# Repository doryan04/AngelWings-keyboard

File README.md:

# Angel Wings Keyboard (by [@ItzAdel](https://github.com/doryan04) and [@nm17](https://github.com/nm17))

.jpg)

# Keymap

The Lower, Raise and Adjust layers are provided to allow you to use full-size keys that are not on this keyboard.

To use one or the other layer, you need to press one of the following keys:
- Super/Enter for Lower.
- Tab/Delete for Raise
- To switch to the Adjust layer, press Enter + Tab / Super + Del

### Check [wiki](https://github.com/ItzAdel/AngelWings-keyboard/wiki/INFO) for more info

# Photos

.jpg)

.jpg)

# Nowadays, this repository is archived
## Check out updates AWF on [my gitea](https://gitea.doryan04.ru/doryan/AWF)

### Check out actual news on Telegram. https://t.me/doryanProjects

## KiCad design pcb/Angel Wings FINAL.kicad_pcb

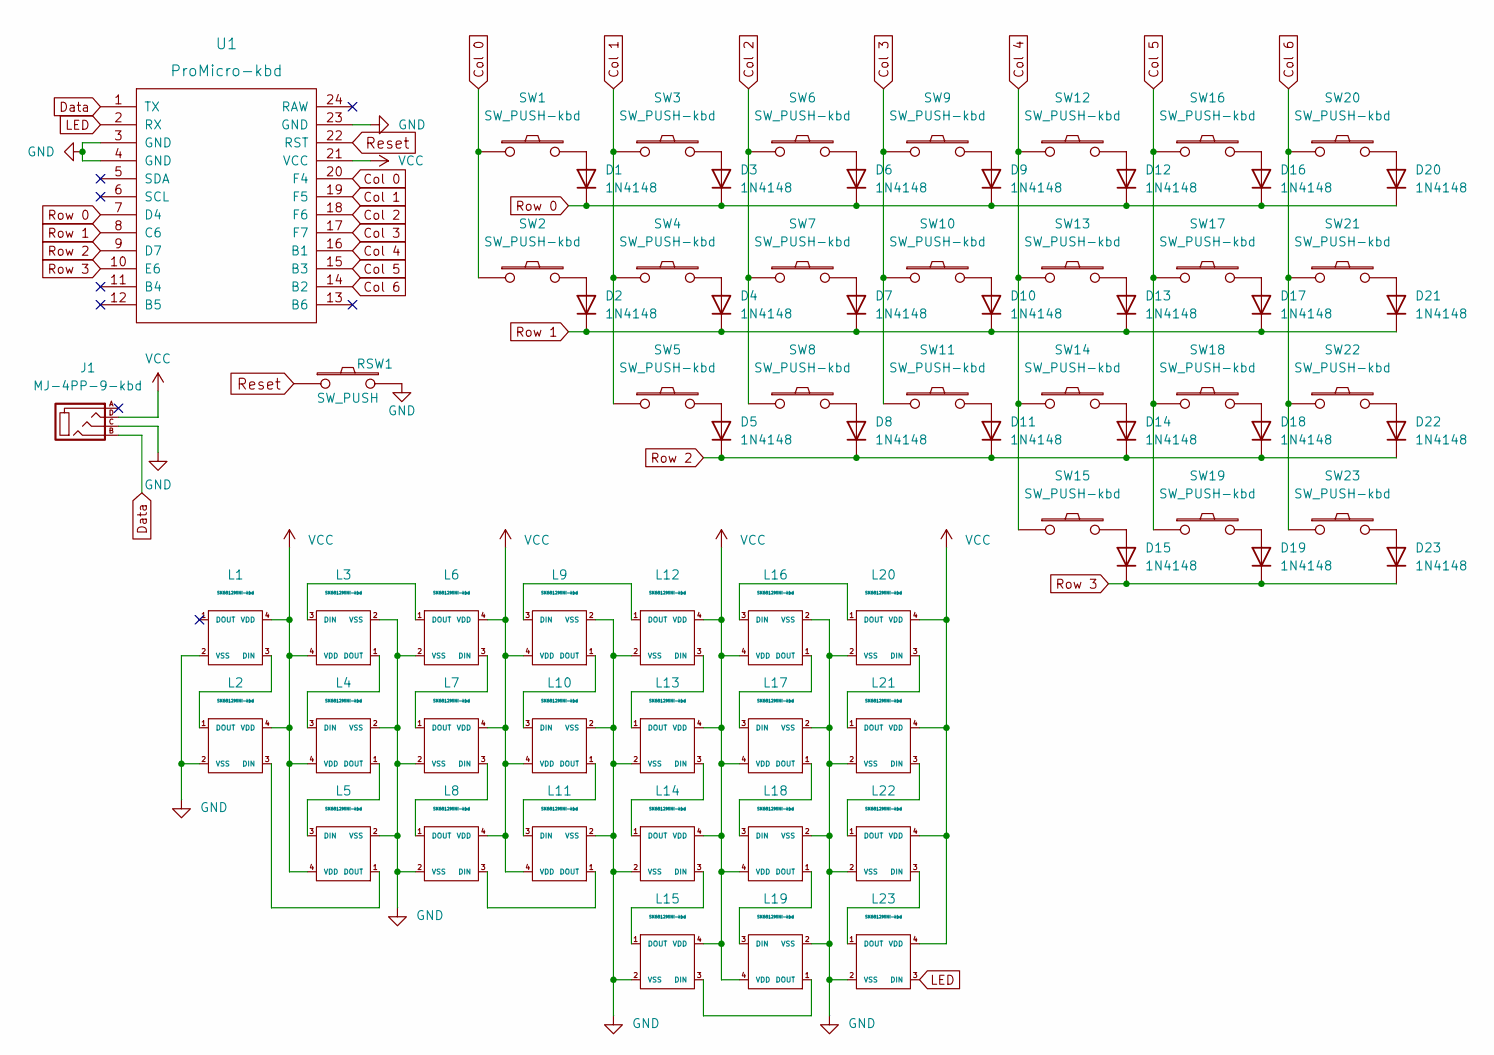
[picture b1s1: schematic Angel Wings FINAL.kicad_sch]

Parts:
D1, D2, D3, D4, D5, D6, D7, D8, D9, D10, D11, D12, D13, D14, D15, D16, D17, D18, D19, D20, D21, D22, D23: 1N4148; D3_TH_SMD
J1: MJ-4PP-9-kbd; MJ-4PP-9
L1, L2, L3, L4, L5, L6, L7, L8, L9, L10, L11, L12, L13, L14, L15, L16, L17, L18, L19, L20, L21, L22, L23: SK6812MINI-kbd; SK6812MINI_rev
RSW1: SW_PUSH; ResetSW
SW1, SW2, SW3, SW4, SW5, SW6, SW7, SW8, SW9, SW10, SW11, SW12, SW13, SW14, SW15, SW16, SW17, SW18, SW19, SW20, SW21, SW22, SW23: SW_PUSH-kbd; MX_ALPS_PG1350_noLed
U1: ProMicro-kbd; ProMicro_v2

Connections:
Col 0: SW1.1, SW2.1, U1.20 (F4)
Col 1: SW3.1, SW4.1, SW5.1, U1.19 (F5)
Col 2: SW6.1, SW7.1, SW8.1, U1.18 (F6)
Col 3: SW9.1, SW10.1, SW11.1, U1.17 (F7)
Col 4: SW12.1, SW13.1, SW14.1, SW15.1, U1.16 (B1)
Col 5: SW16.1, SW17.1, SW18.1, SW19.1, U1.15 (B3)
Col 6: SW20.1, SW21.1, SW22.1, SW23.1, U1.14 (B2)
Data: J1.B, U1.1 (TX)
GND: J1.C, L1.2 (VSS), L2.2 (VSS), L3.2 (VSS), L4.2 (VSS), L5.2 (VSS), L6.2 (VSS), L7.2 (VSS), L8.2 (VSS), L9.2 (VSS), L10.2 (VSS), L11.2 (VSS), L12.2 (VSS), L13.2 (VSS), L14.2 (VSS), L15.2 (VSS), L16.2 (VSS), L17.2 (VSS), L18.2 (VSS), L19.2 (VSS), L20.2 (VSS), L21.2 (VSS), L22.2 (VSS), L23.2 (VSS), RSW1.2, U1.3 (GND), U1.4 (GND), U1.23 (GND)
LED: L23.3 (DIN), U1.2 (RX)
unnamed: D1.2 (A), SW1.2
unnamed: D2.2 (A), SW2.2
unnamed: D3.2 (A), SW3.2
unnamed: D4.2 (A), SW4.2
unnamed: D5.2 (A), SW5.2
unnamed: D6.2 (A), SW6.2
unnamed: D7.2 (A), SW7.2
unnamed: D8.2 (A), SW8.2
unnamed: D9.2 (A), SW9.2
unnamed: D10.2 (A), SW10.2
unnamed: D11.2 (A), SW11.2
unnamed: D12.2 (A), SW12.2
unnamed: D13.2 (A), SW13.2
unnamed: D14.2 (A), SW14.2
unnamed: D15.2 (A), SW15.2
unnamed: D16.2 (A), SW16.2
unnamed: D17.2 (A), SW17.2
unnamed: D18.2 (A), SW18.2
unnamed: D19.2 (A), SW19.2
unnamed: D20.2 (A), SW20.2
unnamed: D21.2 (A), SW21.2
unnamed: D22.2 (A), SW22.2
unnamed: D23.2 (A), SW23.2
unnamed: L1.3 (DIN), L2.1 (DOUT)
unnamed: L2.3 (DIN), L5.1 (DOUT)
unnamed: L3.1 (DOUT), L4.3 (DIN)
unnamed: L3.3 (DIN), L6.1 (DOUT)
unnamed: L4.1 (DOUT), L5.3 (DIN)
unnamed: L6.3 (DIN), L7.1 (DOUT)
unnamed: L7.3 (DIN), L8.1 (DOUT)
unnamed: L10.1 (DOUT), L11.3 (DIN)
unnamed: L9.1 (DOUT), L10.3 (DIN)
unnamed: L8.3 (DIN), L11.1 (DOUT)
unnamed: L9.3 (DIN), L12.1 (DOUT)
unnamed: L12.3 (DIN), L13.1 (DOUT)
unnamed: L13.3 (DIN), L14.1 (DOUT)
unnamed: L14.3 (DIN), L15.1 (DOUT)
unnamed: L15.3 (DIN), L19.1 (DOUT)
unnamed: L16.1 (DOUT), L17.3 (DIN)
unnamed: L16.3 (DIN), L20.1 (DOUT)
unnamed: L17.1 (DOUT), L18.3 (DIN)
unnamed: L18.1 (DOUT), L19.3 (DIN)
unnamed: L20.3 (DIN), L21.1 (DOUT)
unnamed: L21.3 (DIN), L22.1 (DOUT)
unnamed: L22.3 (DIN), L23.1 (DOUT)
Reset: RSW1.1, U1.22 (RST)
Row 0: D1.1 (K), D3.1 (K), D6.1 (K), D9.1 (K), D12.1 (K), D16.1 (K), D20.1 (K), U1.7 (D4)
Row 1: D2.1 (K), D4.1 (K), D7.1 (K), D10.1 (K), D13.1 (K), D17.1 (K), D21.1 (K), U1.8 (C6)
Row 2: D5.1 (K), D8.1 (K), D11.1 (K), D14.1 (K), D18.1 (K), D22.1 (K), U1.9 (D7)
Row 3: D15.1 (K), D19.1 (K), D23.1 (K), U1.10 (E6)
VCC: J1.D, L1.4 (VDD), L2.4 (VDD), L3.4 (VDD), L4.4 (VDD), L5.4 (VDD), L6.4 (VDD), L7.4 (VDD), L8.4 (VDD), L9.4 (VDD), L10.4 (VDD), L11.4 (VDD), L12.4 (VDD), L13.4 (VDD), L14.4 (VDD), L15.4 (VDD), L16.4 (VDD), L17.4 (VDD), L18.4 (VDD), L19.4 (VDD), L20.4 (VDD), L21.4 (VDD), L22.4 (VDD), L23.4 (VDD), U1.21 (VCC)

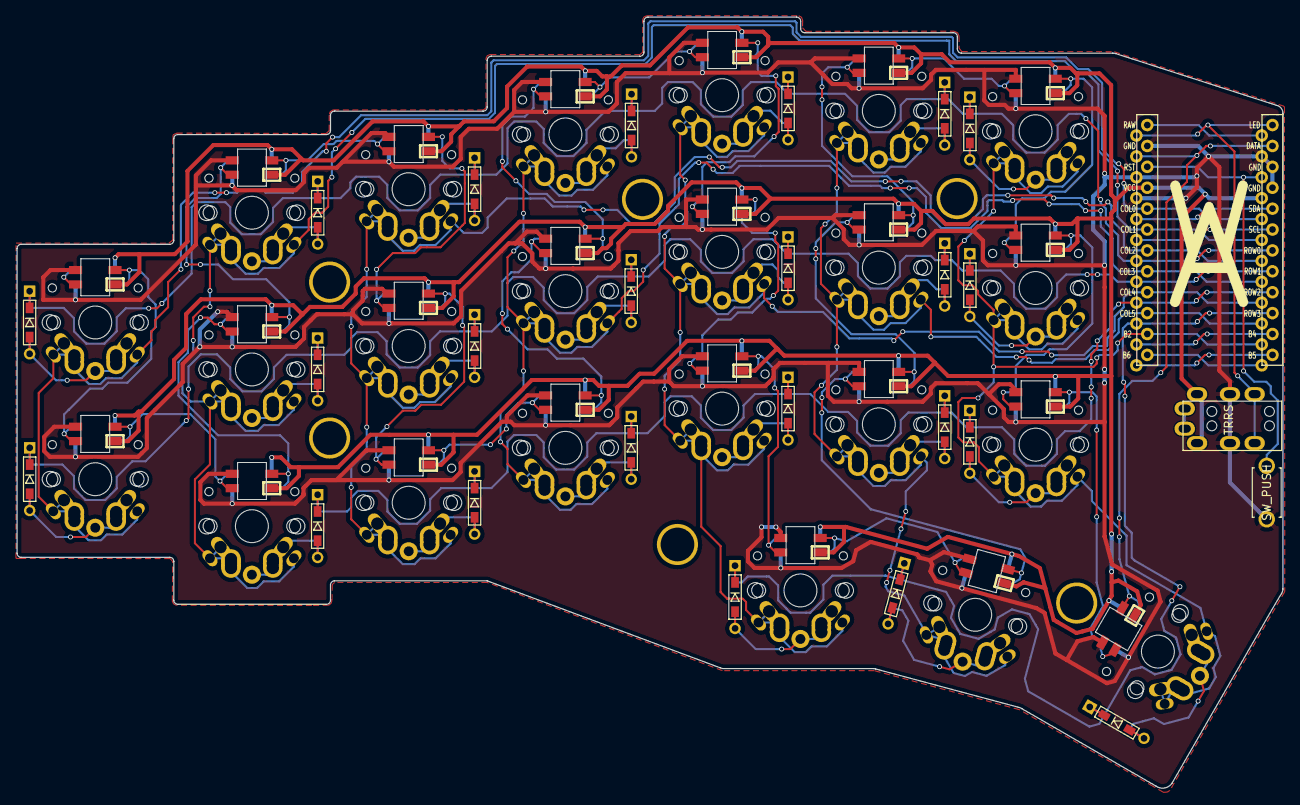
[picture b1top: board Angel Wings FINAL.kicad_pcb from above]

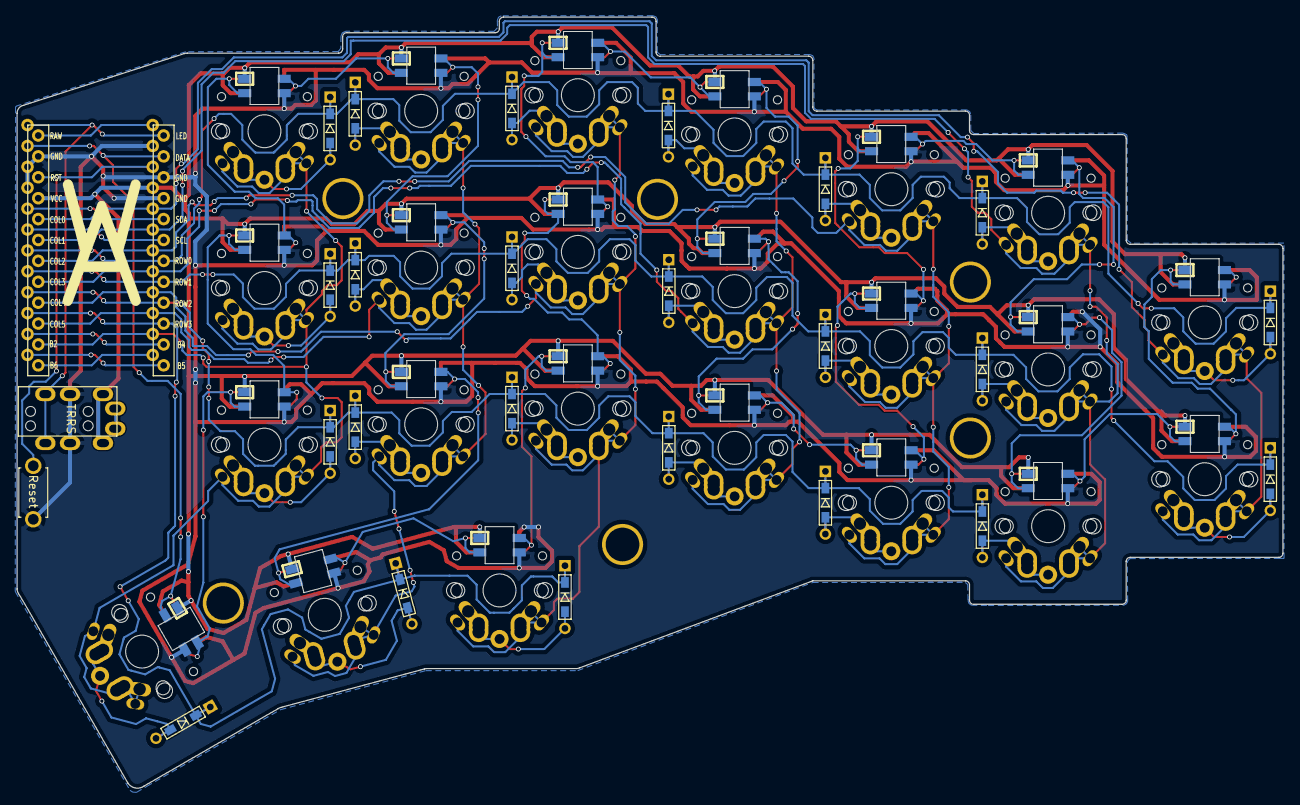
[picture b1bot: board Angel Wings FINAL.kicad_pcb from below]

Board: 2 copper layers, 153.9 x 93.7 mm, 72 parts (23 on the bottom side), 61 nets.

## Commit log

2022-01-01 VIA firmware
2022-01-01 Default firmware
2022-01-01 KiCad files with plates
2022-01-01 KiCad files with pcb
2022-01-01 Gerbers for plates and pcb
2022-01-01 files for compiling firmware
2022-01-01 photo
2022-01-01 files for compiling a firmware
2022-01-07 Draft Definition for VIA
2022-01-07 Fix bugs
2022-01-07 Fixed info.json and fixed bugs in files for firmware
2022-01-07 README.md
2022-01-21 Gerbers PCB, Top plate & Bottom plate
2022-01-21 Angel Wings pcb version 1.1
2022-01-21 Angel Wings pcb version 2.0
2022-01-21 deleted old file
2022-01-21 added images
2022-01-21 Fixed README.md
2022-01-24 fix AWF v.2.1
2022-01-24 Gerbers update
2022-01-24 Photos update
2022-07-06 Add warning (for linux users)
2022-07-06 Some changes.
2022-07-06 Trash remove
2022-07-08 add link on wiki page
2022-07-12 added youtube video
2022-07-12 Add thumbnail for video
2022-07-12 fix size thumb
2022-07-14 README.md update
2022-07-14 New gerber AWF 2.2 pcb
2022-07-14 Add AWF 2.2
2022-07-14 Adding compressed images
2022-07-14 Add STL cases for MX and Choc + add DXF plate
2022-07-14 Deleted old PCB ver. 2
2022-07-14 Deleted old version PCB
2022-07-14 New PCB photo
2022-07-14 Deleted rubbish
2022-07-14 Remove rubbish
2022-07-20 Add RGB effects
2022-07-20 Add extra layout
2022-07-20 Firmware update
2022-07-20 Keymap, RGB light conf update
2022-07-20 Add layout 3x6
2022-07-20 Add RGB light effects
2022-07-20 Add 3x7 and 3x6 layouts
2022-07-20 Remove trash
2022-07-26 Update keymap
2022-07-27 Add a picture with a keymap
2022-08-29 Changed Telegram channel link
2022-09-18 removed rgb customization from via in json, edited keymap via
2023-03-08 hotfix
